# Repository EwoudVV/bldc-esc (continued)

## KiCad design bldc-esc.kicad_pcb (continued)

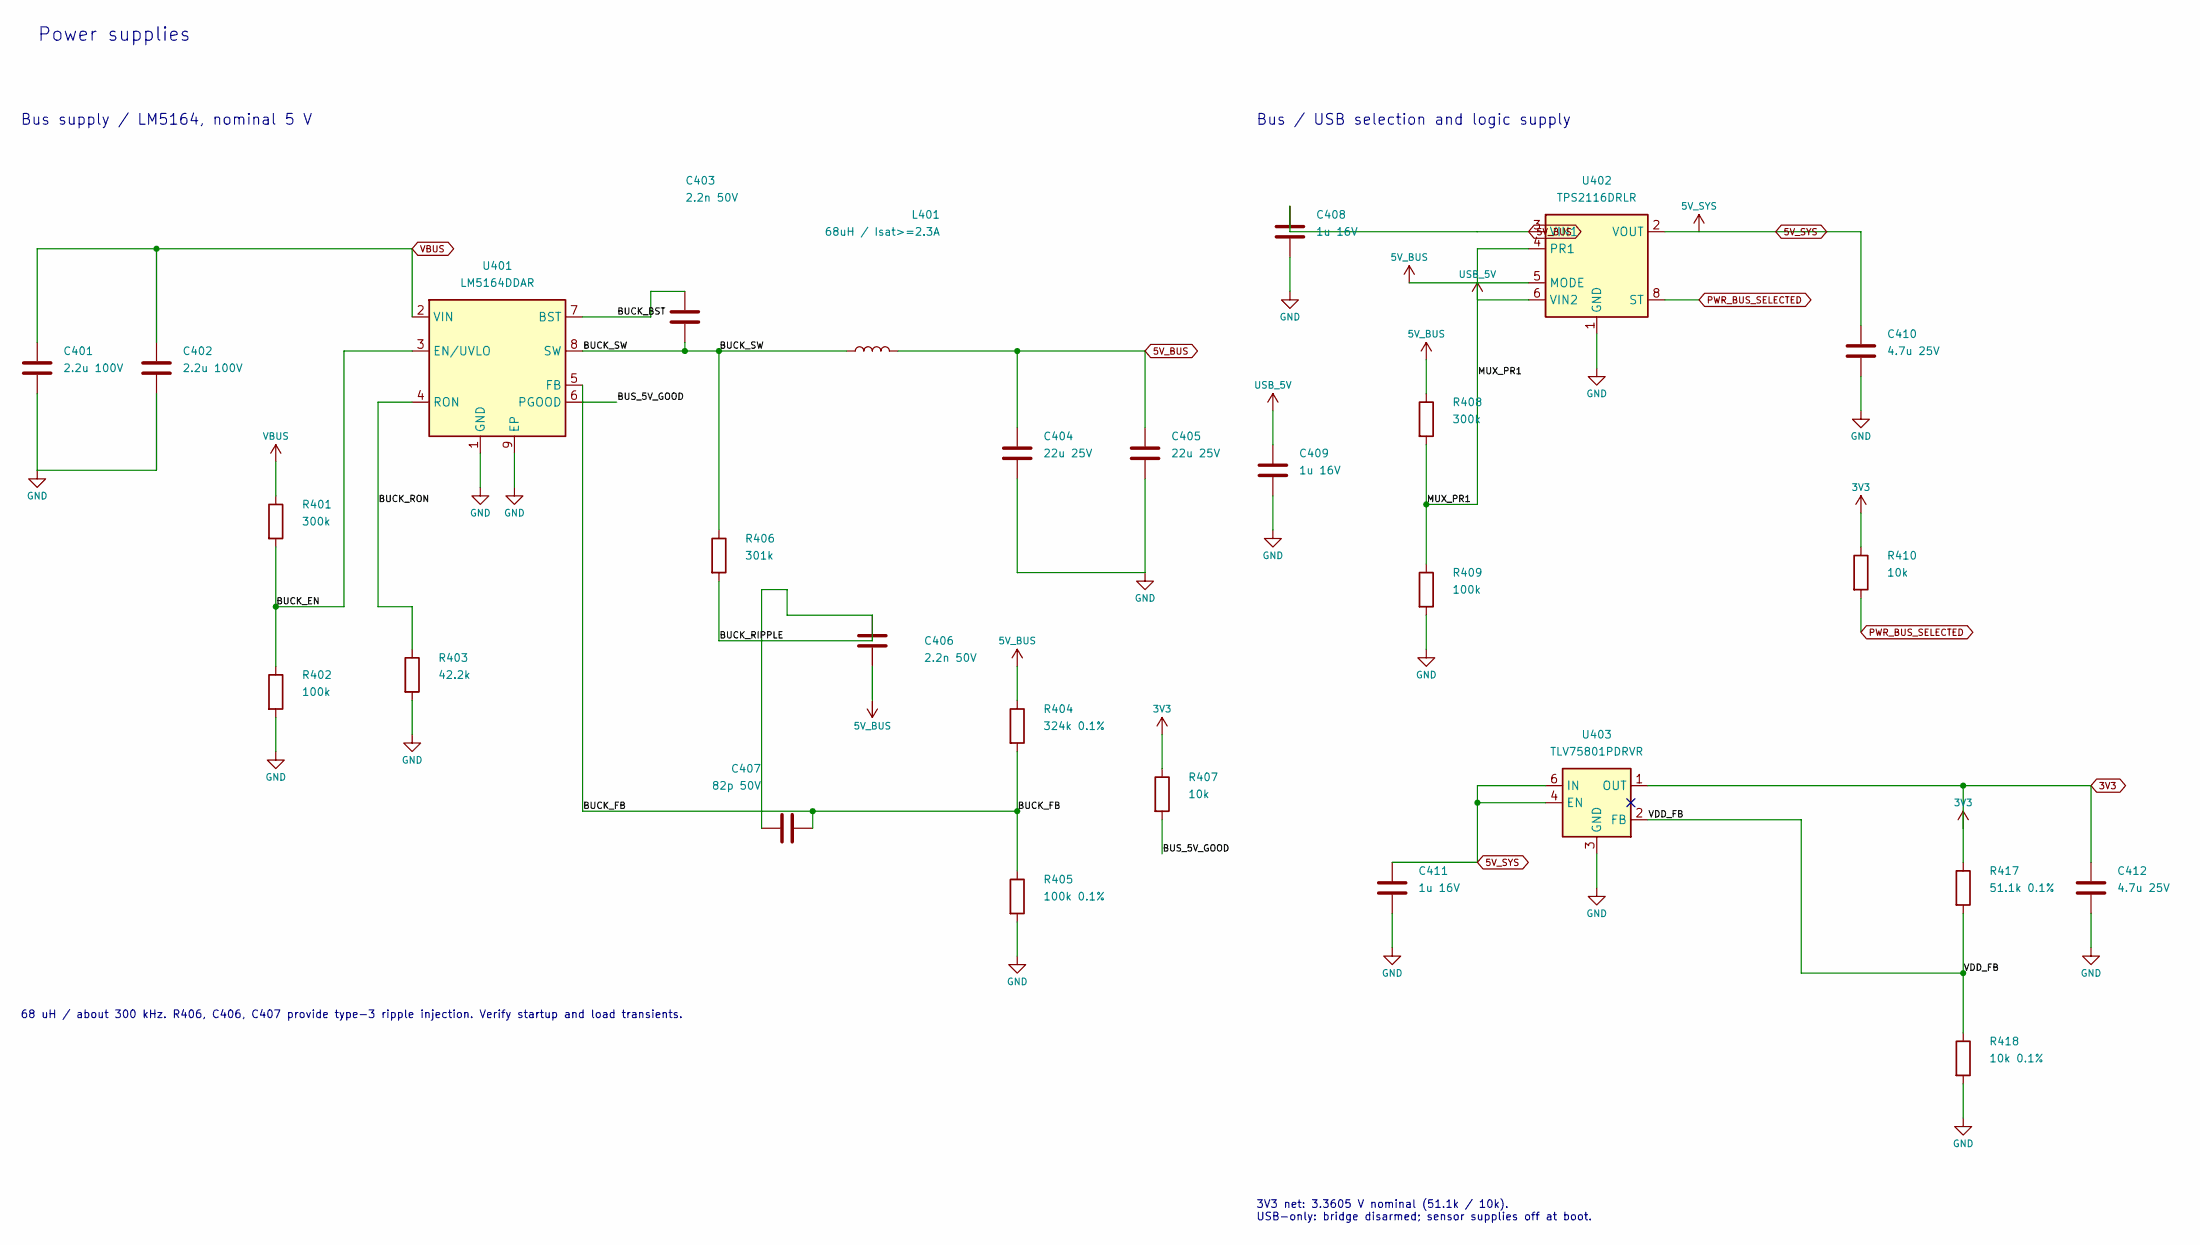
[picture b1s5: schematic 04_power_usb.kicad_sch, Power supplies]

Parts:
C401, C402: 2.2u 100V; C_1210_3225Metric; MPN CGA6N3X7R2A225K230AB
C403, C406: 2.2n 50V; C_0603_1608Metric; MPN C0603C222J5GACTU
C404, C405: 22u 25V; C_1210_3225Metric; MPN MSAST32MSB7226KPNB25
C407: 82p 50V; C_0603_1608Metric; MPN C0603C820J5GACTU
C408, C409, C411: 1u 16V; C_0603_1608Metric; MPN C0603C105K4RACTU
C410, C412: 4.7u 25V; C_0805_2012Metric; MPN C0805C475K3RACTU
L401: 68uH / Isat>=2.3A; L_Coilcraft_MSS1246T-XXX; MPN MSS1246T-683MLC
R401, R408: 300k; R_0603_1608Metric; MPN RC0603FR-07300KL
R402, R409: 100k; R_0603_1608Metric; MPN RC0603FR-07100KL
R403: 42.2k; R_0603_1608Metric; MPN RC0603FR-0742K2L
R404: 324k 0.1%; R_0603_1608Metric; MPN RT0603BRD07324KL
R405: 100k 0.1%; R_0603_1608Metric; MPN RT0603BRD07100KL
R406: 301k; R_0603_1608Metric; MPN RC0603FR-07301KL
R407, R410: 10k; R_0603_1608Metric; MPN RC0603FR-0710KL
R417: 51.1k 0.1%; R_0603_1608Metric; MPN RT0603BRD0751K1L
R418: 10k 0.1%; R_0603_1608Metric; MPN RT0603BRD0710KL
U401: LM5164DDAR; HSOP-8-1EP_3.9x4.9mm_P1.27mm_EP2.41x3.1mm_ThermalVias; MPN LM5164DDAR
U402: TPS2116DRLR; SOT-583-8; MPN TPS2116DRLR
U403: TLV75801PDRVR; WSON-6-1EP_2x2mm_P0.65mm_EP1x1.6mm; MPN TLV75801PDRVR

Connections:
3V3: C412.1, R407.1, R410.1, R417.1, U403.1 (OUT); also elsewhere on the board
5V_BUS: C404.1, C405.1, C406.2, C408.1, L401.2, R404.1, R408.1, U402.3 (VIN1), U402.5 (MODE); also elsewhere on the board
5V_SYS: C410.1, C411.1, U402.2 (VOUT), U402.7 (VOUT), U403.4 (EN), U403.6 (IN); also elsewhere on the board
/04_power_usb/BUCK_BST: C403.1, U401.7 (BST)
/04_power_usb/BUCK_EN: R401.2, R402.1, U401.3 (EN/UVLO)
/04_power_usb/BUCK_FB: C407.2, R404.2, R405.1, U401.5 (FB)
/04_power_usb/BUCK_RIPPLE: C406.1, C407.1, R406.2
/04_power_usb/BUCK_RON: R403.1, U401.4 (RON)
/04_power_usb/BUCK_SW: C403.2, L401.1, R406.1, U401.8 (SW)
/04_power_usb/BUS_5V_GOOD: R407.2, U401.6 (PGOOD)
/04_power_usb/VDD_FB: R417.2, R418.1, U403.2 (FB)
PWR_BUS_SELECTED: R410.2, U402.8 (ST); also elsewhere on the board
VBUS: C401.1, C402.1, R401.1, U401.2 (VIN); also elsewhere on the board

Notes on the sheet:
Power supplies
Bus supply / LM5164, nominal 5 V
68 uH / about 300 kHz. R406, C406, C407 provide type-3 ripple injection. Verify startup and load transients.
Bus / USB selection and logic supply
3V3 net: 3.3605 V nominal (51.1k / 10k). USB-only: bridge disarmed; sensor supplies off at boot.

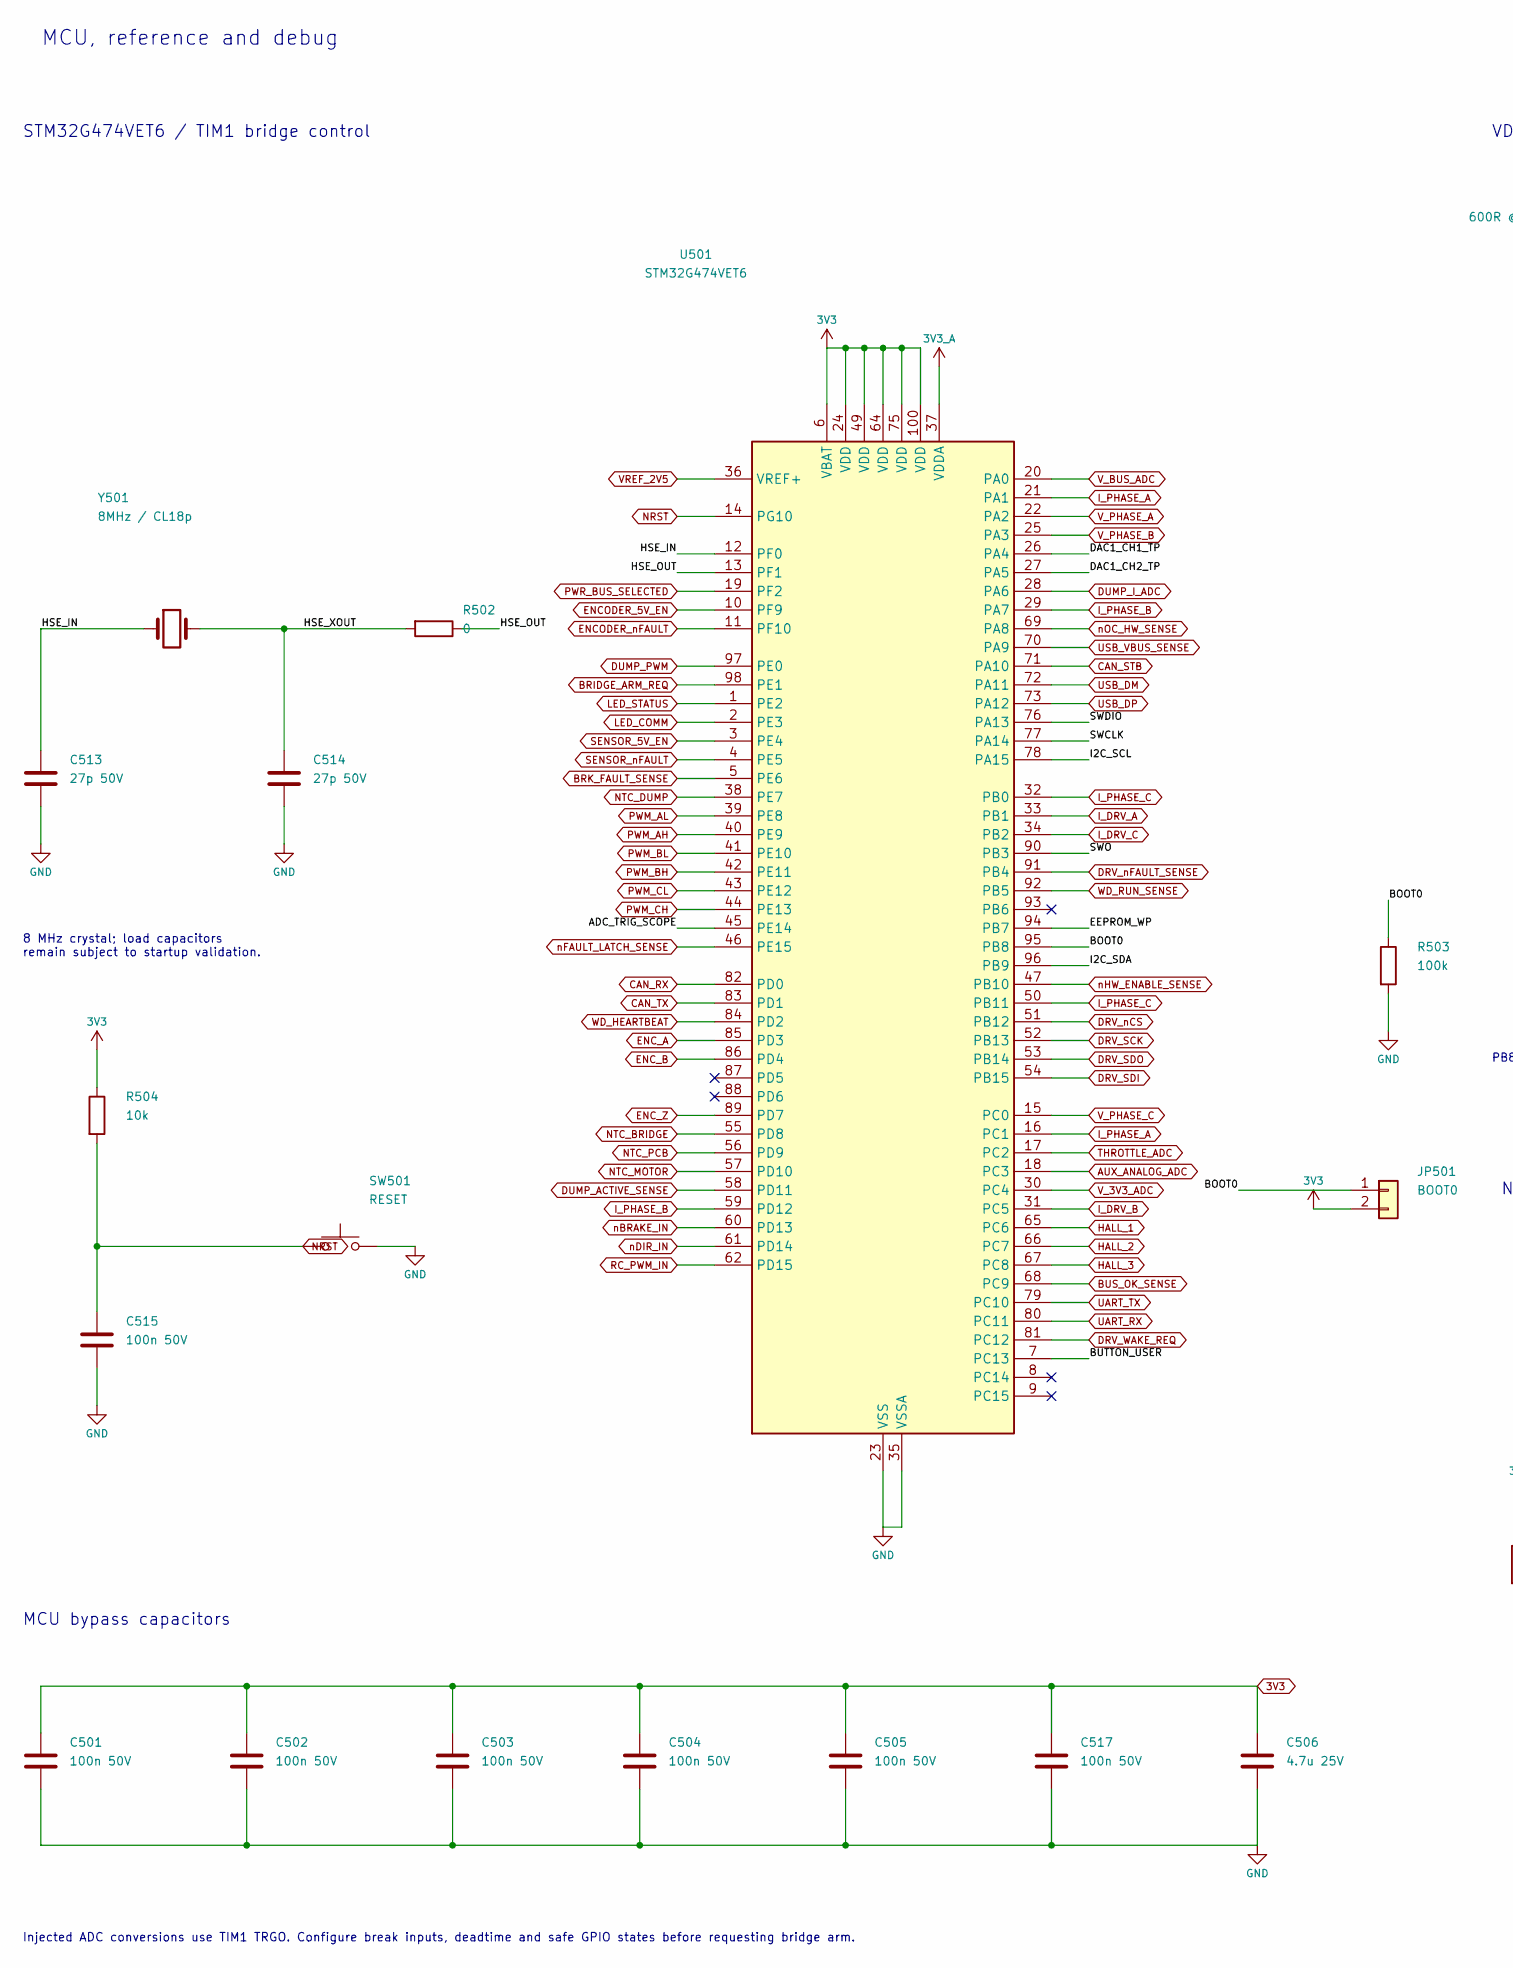
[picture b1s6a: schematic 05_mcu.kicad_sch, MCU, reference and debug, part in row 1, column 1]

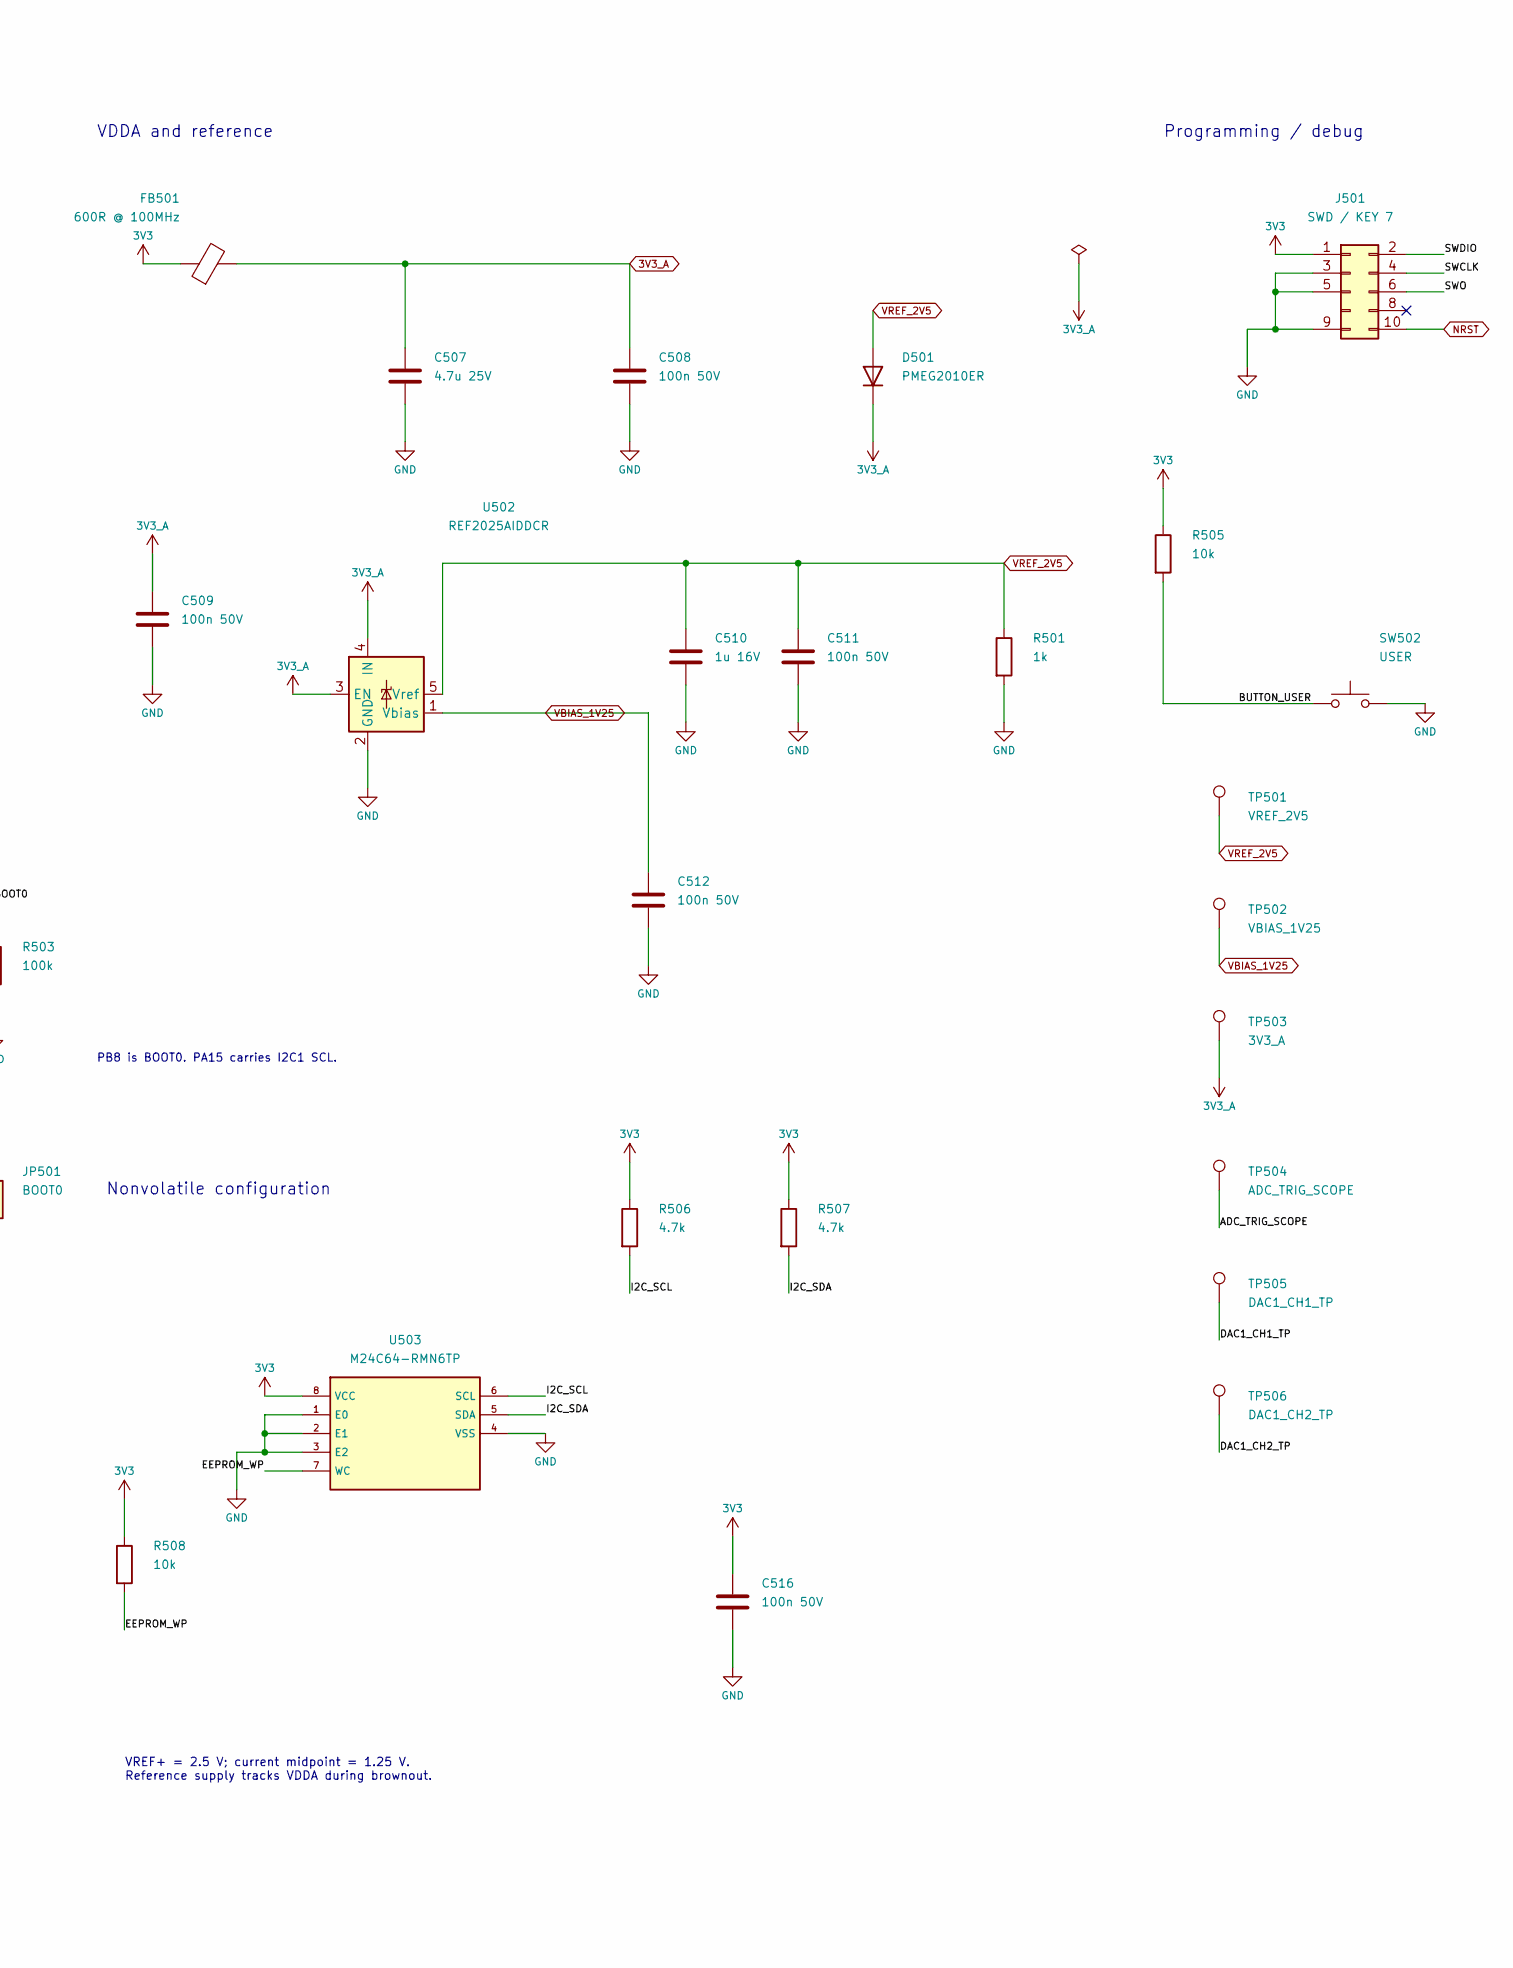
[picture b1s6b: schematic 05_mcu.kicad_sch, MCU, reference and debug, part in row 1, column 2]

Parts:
C501, C502, C503, C504, C505, C508, C509, C511, C512, C515, C516, C517: 100n 50V; C_0603_1608Metric; MPN C0603C104K5RACTU
C506, C507: 4.7u 25V; C_0805_2012Metric; MPN C0805C475K3RACTU
C510: 1u 16V; C_0603_1608Metric; MPN C0603C105K4RACTU
C513, C514: 27p 50V; C_0603_1608Metric; MPN C0603C270J5GACTU
D501: PMEG2010ER; Nexperia_CFP3_SOD-123W; MPN PMEG2010ER,115
FB501: 600R @ 100MHz; L_0603_1608Metric; MPN BLM18KG601SN1D
J501: SWD / KEY 7; FTSH_105_DV_007_K; MPN FTSH-105-01-L-DV-007-K
JP501: BOOT0; PinHeader_1x02_P2.54mm_Vertical; MPN M20-9990245
R501: 1k; R_0603_1608Metric; MPN RC0603FR-071KL
R502: 0; R_0603_1608Metric; MPN RC0603JR-070RL
R503: 100k; R_0603_1608Metric; MPN RC0603FR-07100KL
R504, R505, R508: 10k; R_0603_1608Metric; MPN RC0603FR-0710KL
R506, R507: 4.7k; R_0603_1608Metric; MPN RC0603FR-074K7L
SW501: RESET; SW_SPST_TL3342; MPN TL3342F160QG
SW502: USER; SW_SPST_TL3342; MPN TL3342F160QG
TP501: VREF_2V5; TestPoint_Pad_D1.5mm; MPN TESTPOINT
TP502: VBIAS_1V25; TestPoint_Pad_D1.5mm; MPN TESTPOINT
TP503: 3V3_A; TestPoint_Pad_D1.5mm; MPN TESTPOINT
TP504: ADC_TRIG_SCOPE; TestPoint_Pad_D1.5mm; MPN TESTPOINT
TP505: DAC1_CH1_TP; TestPoint_Pad_D1.5mm; MPN TESTPOINT
TP506: DAC1_CH2_TP; TestPoint_Pad_D1.5mm; MPN TESTPOINT
U501: STM32G474VET6; LQFP-100_14x14mm_P0.5mm; MPN STM32G474VET6
U502: REF2025AIDDCR; SOT-23-5; MPN REF2025AIDDCR
U503: M24C64-RMN6TP; SOIC-8_3.9x4.9mm_P1.27mm; MPN M24C64-RMN6TP
Y501: 8MHz / CL18p; Crystal_SMD_Abracon_ABM3-2Pin_5.0x3.2mm; MPN ABM3-8.000MHZ-D2Y-T

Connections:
3V3: C501.1, C502.1, C503.1, C504.1, C505.1, C506.1, C516.1, C517.1, FB501.1, J501.1, JP501.2, R504.1, R505.1, R506.1, R507.1, R508.1, U501.6 (VBAT), U501.24 (VDD), U501.49 (VDD), U501.64 (VDD), U501.75 (VDD), U501.100 (VDD), U503.8 (VCC); also elsewhere on the board
3V3_A: C507.1, C508.1, C509.1, D501.1 (K), FB501.2, TP503.1 (1_1), U501.37 (VDDA), U502.3 (EN), U502.4 (IN); also elsewhere on the board
/05_mcu/ADC_TRIG_SCOPE: TP504.1 (1_1), U501.45 (PE14)
/05_mcu/BOOT0: JP501.1, R503.1, U501.95 (PB8)
/05_mcu/BUTTON_USER: R505.2, SW502.1, U501.7 (PC13)
/05_mcu/DAC1_CH1_TP: TP505.1 (1_1), U501.26 (PA4)
/05_mcu/DAC1_CH2_TP: TP506.1 (1_1), U501.27 (PA5)
/05_mcu/EEPROM_WP: R508.2, U501.94 (PB7), U503.7 (WC)
/05_mcu/HSE_IN: C513.1, U501.12 (PF0), Y501.1
/05_mcu/HSE_OUT: R502.1, U501.13 (PF1)
/05_mcu/HSE_XOUT: C514.1, R502.2, Y501.2
/05_mcu/I2C_SCL: R506.2, U501.78 (PA15), U503.6 (SCL)
/05_mcu/I2C_SDA: R507.2, U501.96 (PB9), U503.5 (SDA)
/05_mcu/SWCLK: J501.4, U501.77 (PA14)
/05_mcu/SWDIO: J501.2, U501.76 (PA13)
/05_mcu/SWO: J501.6, U501.90 (PB3)
AUX_ANALOG_ADC: U501.18 (PC3); also elsewhere on the board
BRIDGE_ARM_REQ: U501.98 (PE1); also elsewhere on the board
BRK_FAULT_SENSE: U501.5 (PE6); also elsewhere on the board
BUS_OK_SENSE: U501.68 (PC9); also elsewhere on the board
CAN_RX: U501.82 (PD0); also elsewhere on the board
CAN_STB: U501.71 (PA10); also elsewhere on the board
CAN_TX: U501.83 (PD1); also elsewhere on the board
DRV_SCK: U501.52 (PB13); also elsewhere on the board
DRV_SDI: U501.54 (PB15); also elsewhere on the board
DRV_SDO: U501.53 (PB14); also elsewhere on the board
DRV_WAKE_REQ: U501.81 (PC12); also elsewhere on the board
DRV_nCS: U501.51 (PB12); also elsewhere on the board
DRV_nFAULT_SENSE: U501.91 (PB4); also elsewhere on the board
DUMP_ACTIVE_SENSE: U501.58 (PD11); also elsewhere on the board
DUMP_I_ADC: U501.28 (PA6); also elsewhere on the board
DUMP_PWM: U501.97 (PE0); also elsewhere on the board
ENCODER_5V_EN: U501.10 (PF9); also elsewhere on the board
ENCODER_nFAULT: U501.11 (PF10); also elsewhere on the board
ENC_A: U501.85 (PD3); also elsewhere on the board
ENC_B: U501.86 (PD4); also elsewhere on the board
ENC_Z: U501.89 (PD7); also elsewhere on the board
HALL_1: U501.65 (PC6); also elsewhere on the board
HALL_2: U501.66 (PC7); also elsewhere on the board
HALL_3: U501.67 (PC8); also elsewhere on the board
I_DRV_A: U501.33 (PB1); also elsewhere on the board
I_DRV_B: U501.31 (PC5); also elsewhere on the board
I_DRV_C: U501.34 (PB2); also elsewhere on the board
I_PHASE_A: U501.16 (PC1), U501.21 (PA1); also elsewhere on the board
I_PHASE_B: U501.29 (PA7), U501.59 (PD12); also elsewhere on the board
I_PHASE_C: U501.32 (PB0), U501.50 (PB11); also elsewhere on the board
LED_COMM: U501.2 (PE3); also elsewhere on the board
LED_STATUS: U501.1 (PE2); also elsewhere on the board
NRST: C515.1, J501.10, R504.2, SW501.1, U501.14 (PG10); also elsewhere on the board
NTC_BRIDGE: U501.55 (PD8); also elsewhere on the board
NTC_DUMP: U501.38 (PE7); also elsewhere on the board
NTC_MOTOR: U501.57 (PD10); also elsewhere on the board
NTC_PCB: U501.56 (PD9); also elsewhere on the board
PWM_AH: U501.40 (PE9); also elsewhere on the board
PWM_AL: U501.39 (PE8); also elsewhere on the board
PWM_BH: U501.42 (PE11); also elsewhere on the board
PWM_BL: U501.41 (PE10); also elsewhere on the board
PWM_CH: U501.44 (PE13); also elsewhere on the board
PWM_CL: U501.43 (PE12); also elsewhere on the board
PWR_BUS_SELECTED: U501.19 (PF2); also elsewhere on the board
RC_PWM_IN: U501.62 (PD15); also elsewhere on the board
SENSOR_5V_EN: U501.3 (PE4); also elsewhere on the board
SENSOR_nFAULT: U501.4 (PE5); also elsewhere on the board
THROTTLE_ADC: U501.17 (PC2); also elsewhere on the board
UART_RX: U501.80 (PC11); also elsewhere on the board
UART_TX: U501.79 (PC10); also elsewhere on the board
USB_DM: U501.72 (PA11); also elsewhere on the board
USB_DP: U501.73 (PA12); also elsewhere on the board
USB_VBUS_SENSE: U501.70 (PA9); also elsewhere on the board
VBIAS_1V25: C512.1, TP502.1 (1_1), U502.1 (Vbias); also elsewhere on the board
VREF_2V5: C510.1, C511.1, D501.2 (A), R501.1, TP501.1 (1_1), U501.36 (VREF+), U502.5 (Vref); also elsewhere on the board
V_3V3_ADC: U501.30 (PC4); also elsewhere on the board
V_BUS_ADC: U501.20 (PA0); also elsewhere on the board
V_PHASE_A: U501.22 (PA2); also elsewhere on the board
V_PHASE_B: U501.25 (PA3); also elsewhere on the board
V_PHASE_C: U501.15 (PC0); also elsewhere on the board
WD_HEARTBEAT: U501.84 (PD2); also elsewhere on the board
WD_RUN_SENSE: U501.92 (PB5); also elsewhere on the board
nBRAKE_IN: U501.60 (PD13); also elsewhere on the board
nDIR_IN: U501.61 (PD14); also elsewhere on the board
nFAULT_LATCH_SENSE: U501.46 (PE15); also elsewhere on the board
nHW_ENABLE_SENSE: U501.47 (PB10); also elsewhere on the board
nOC_HW_SENSE: U501.69 (PA8); also elsewhere on the board

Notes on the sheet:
MCU, reference and debug
STM32G474VET6 / TIM1 bridge control
VDDA and reference
MCU bypass capacitors
8 MHz crystal; load capacitors remain subject to startup validation.
PB8 is BOOT0. PA15 carries I2C1 SCL.
Nonvolatile configuration
Programming / debug
VREF+ = 2.5 V; current midpoint = 1.25 V. Reference supply tracks VDDA during brownout.
Injected ADC conversions use TIM1 TRGO. Configure break inputs, deadtime and safe GPIO states before requesting bridge arm.

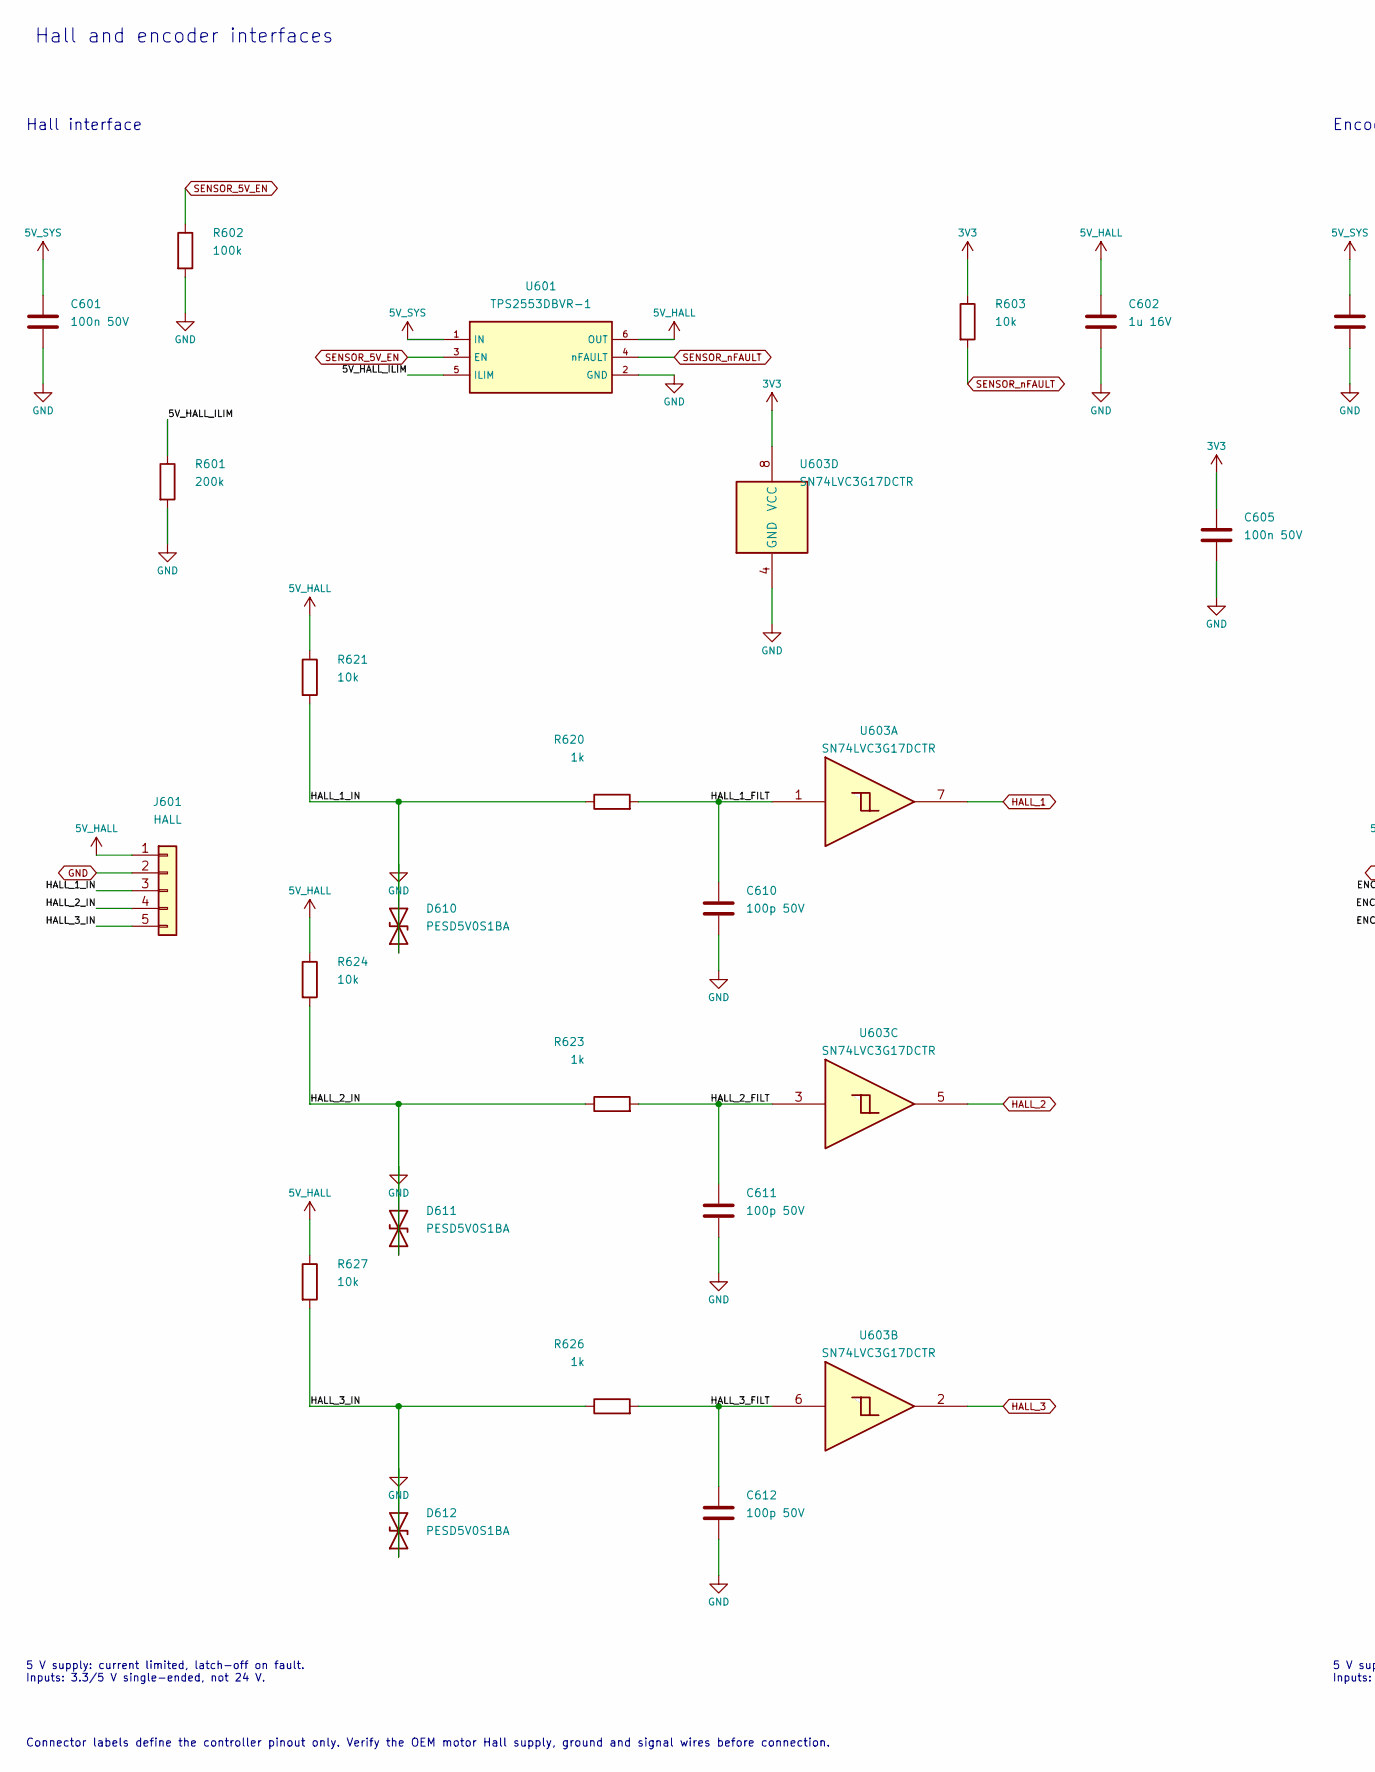
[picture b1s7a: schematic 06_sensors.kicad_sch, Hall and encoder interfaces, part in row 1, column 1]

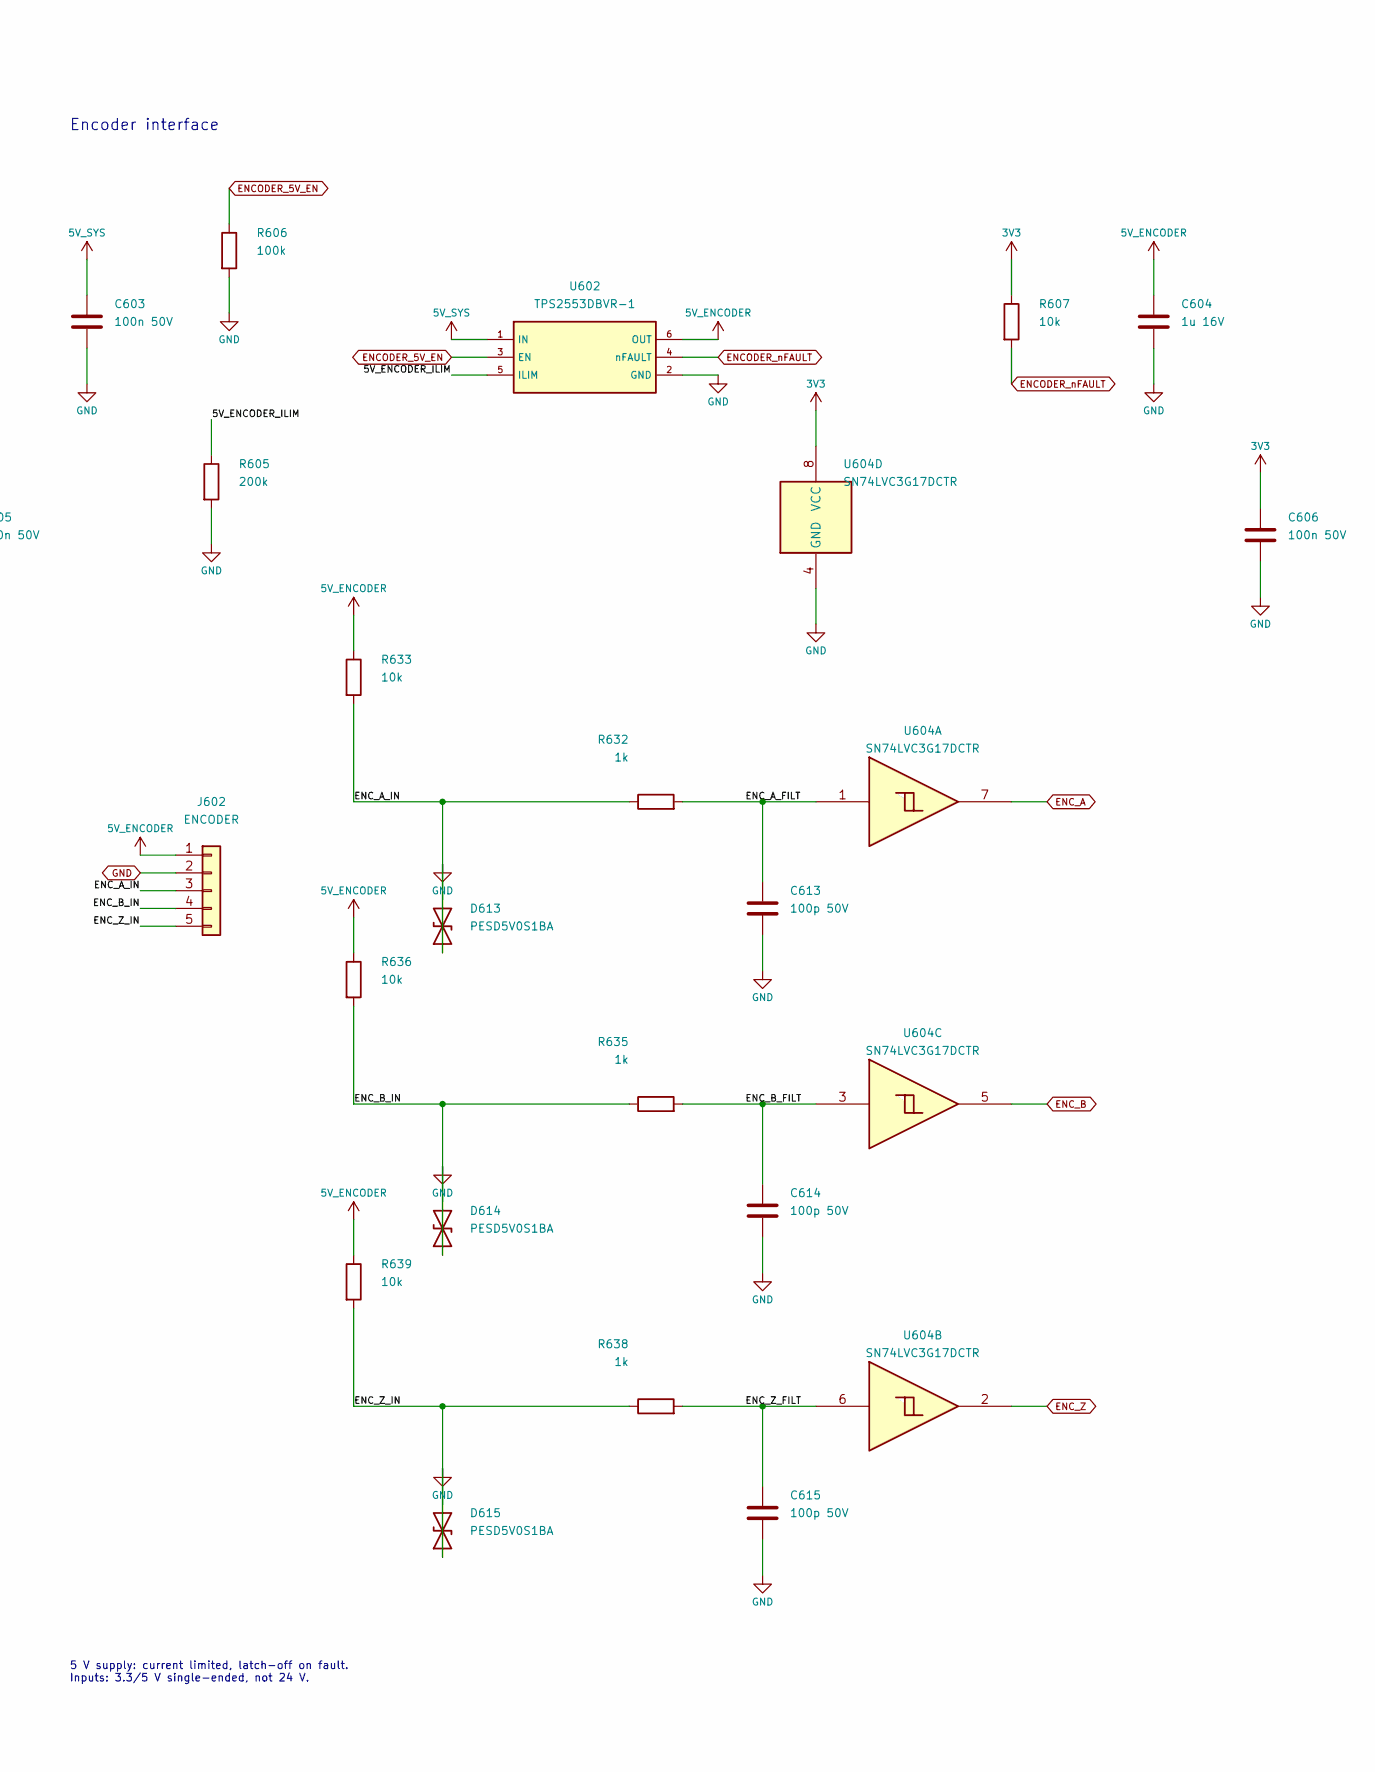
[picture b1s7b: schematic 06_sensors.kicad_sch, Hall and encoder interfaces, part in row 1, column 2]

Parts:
C601, C603, C605, C606: 100n 50V; C_0603_1608Metric; MPN C0603C104K5RACTU
C602, C604: 1u 16V; C_0603_1608Metric; MPN C0603C105K4RACTU
C610, C611, C612, C613, C614, C615: 100p 50V; C_0603_1608Metric; MPN C0603C101J5GACTU
D610, D611, D612, D613, D614, D615: PESD5V0S1BA; D_SOD-323; MPN PESD5V0S1BA,115
J601: HALL; JST_GH_BM05B-GHS-TBT_1x05-1MP_P1.25mm_Vertical; MPN BM05B-GHS-TBT(LF)(SN)
J602: ENCODER; JST_GH_BM05B-GHS-TBT_1x05-1MP_P1.25mm_Vertical; MPN BM05B-GHS-TBT(LF)(SN)
R601, R605: 200k; R_0603_1608Metric; MPN RC0603FR-07200KL
R602, R606: 100k; R_0603_1608Metric; MPN RC0603FR-07100KL
R603, R607, R621, R624, R627, R633, R636, R639: 10k; R_0603_1608Metric; MPN RC0603FR-0710KL
R620, R623, R626, R632, R635, R638: 1k; R_0603_1608Metric; MPN RC0603FR-071KL
U601, U602: TPS2553DBVR-1; SOT-23-6; MPN TPS2553DBVR-1
U603, U604: SN74LVC3G17DCTR; SSOP-8_2.95x2.8mm_P0.65mm; MPN SN74LVC3G17DCTR

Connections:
3V3: C605.1, C606.1, R603.1, R607.1, U603.8 (VCC), U604.8 (VCC); also elsewhere on the board
5V_ENCODER: C604.1, J602.1, R633.1, R636.1, R639.1, U602.6 (OUT)
5V_HALL: C602.1, J601.1, R621.1, R624.1, R627.1, U601.6 (OUT); also elsewhere on the board
5V_SYS: C601.1, C603.1, U601.1 (IN), U602.1 (IN); also elsewhere on the board
/06_sensors/5V_ENCODER_ILIM: R605.1, U602.5 (ILIM)
/06_sensors/5V_HALL_ILIM: R601.1, U601.5 (ILIM)
/06_sensors/ENC_A_FILT: C613.1, R632.2, U604.1
/06_sensors/ENC_B_FILT: C614.1, R635.2, U604.3
/06_sensors/ENC_Z_FILT: C615.1, R638.2, U604.6
/06_sensors/HALL_1_FILT: C610.1, R620.2, U603.1
/06_sensors/HALL_2_FILT: C611.1, R623.2, U603.3
/06_sensors/HALL_3_FILT: C612.1, R626.2, U603.6
ENCODER_5V_EN: R606.1, U602.3 (EN); also elsewhere on the board
ENCODER_nFAULT: R607.2, U602.4 (nFAULT); also elsewhere on the board
ENC_A: U604.7; also elsewhere on the board
ENC_B: U604.5; also elsewhere on the board
ENC_Z: U604.2; also elsewhere on the board
HALL_1: U603.7; also elsewhere on the board
HALL_2: U603.5; also elsewhere on the board
HALL_3: U603.2; also elsewhere on the board
SENSOR_5V_EN: R602.1, U601.3 (EN); also elsewhere on the board
SENSOR_nFAULT: R603.2, U601.4 (nFAULT); also elsewhere on the board

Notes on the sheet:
Hall and encoder interfaces
Hall interface
5 V supply: current limited, latch-off on fault. Inputs: 3.3/5 V single-ended, not 24 V.
Encoder interface
Connector labels define the controller pinout only. Verify the OEM motor Hall supply, ground and signal wires before connection.
